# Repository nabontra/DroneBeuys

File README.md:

# DroneBeuys project documentation

#Ceiling String Pull
24vcd stepper motor and fishing line

#Smoke Lamp
12vdc lamp and e-cigarette

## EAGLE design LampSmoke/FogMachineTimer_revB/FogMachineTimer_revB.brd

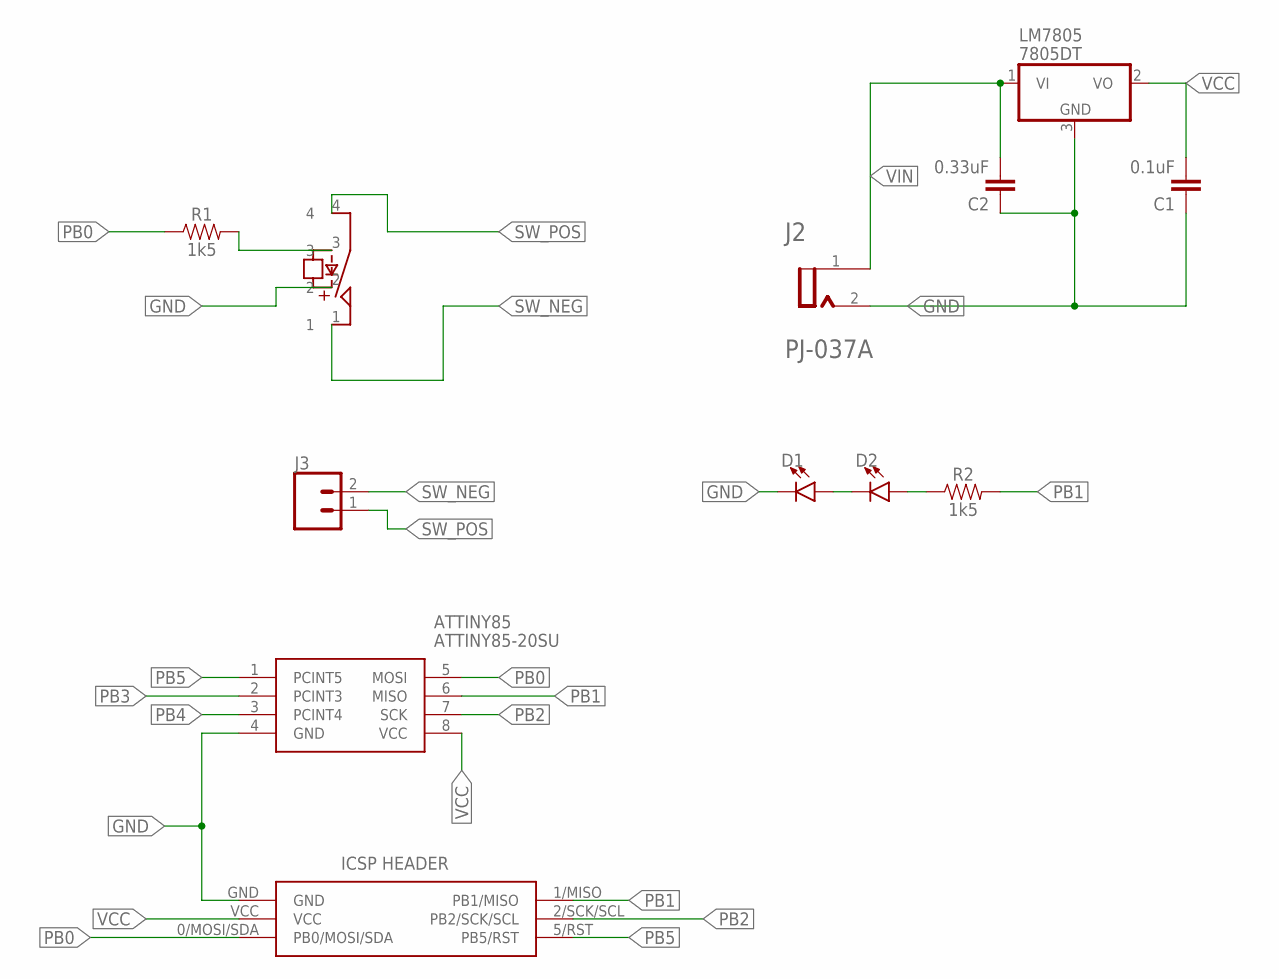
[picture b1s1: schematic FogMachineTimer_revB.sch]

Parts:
ATTINY85: ATTINY85-20SU; SOT127P798X216-8N
C1: 0.1uF; 0603
C2: 0.33uF; 0603
D1, D2: LED1206; LED-1206
J1: M20-9980346; HDRV6W64P254_2X3_762X508X868P
J2: CUI_PJ-037ACUI_PJ-037A_0_0; CUI_PJ-037A_0
J3: CONN_02; 1X02
LM7805: 7805DT; TO252
R1, R2: 1k5; 0603
RELAY: HE3621A0510

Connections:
GND: ATTINY85.4 (GND), C1.1, C2.1, D1.C, J1.GND, J2.2, LM7805.3 (GND), RELAY.2
unnamed: D1.A, D2.C
unnamed: D2.A, R2.1
unnamed: R1.2, RELAY.3
PB0: ATTINY85.5 (MOSI), J1.0/MOSI/SDA (PB0/MOSI/SDA), R1.1
PB1: ATTINY85.6 (MISO), J1.1/MISO (PB1/MISO), R2.2
PB2: ATTINY85.7 (SCK), J1.2/SCK/SCL (PB2/SCK/SCL)
PB3: ATTINY85.2 (PCINT3)
PB4: ATTINY85.3 (PCINT4)
PB5: ATTINY85.1 (PCINT5), J1.5/RST (PB5/RST)
SW_NEG: J3.2, RELAY.1
SW_POS: J3.1, RELAY.4
VCC: ATTINY85.8 (VCC), C1.2, J1.VCC, LM7805.2 (VO)
VIN: C2.2, J2.1, LM7805.1 (VI)

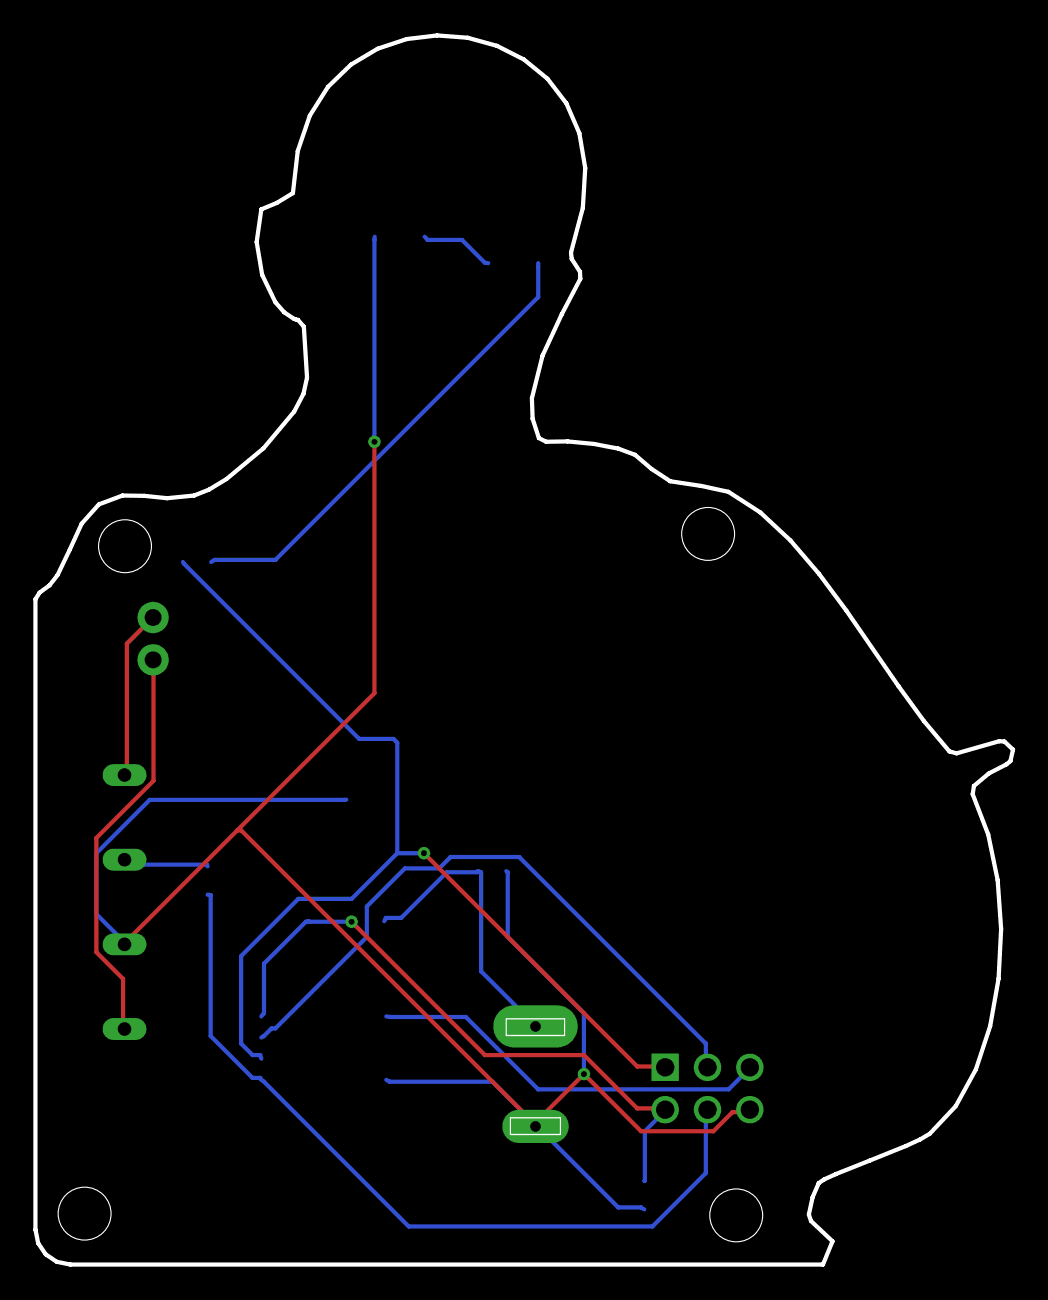
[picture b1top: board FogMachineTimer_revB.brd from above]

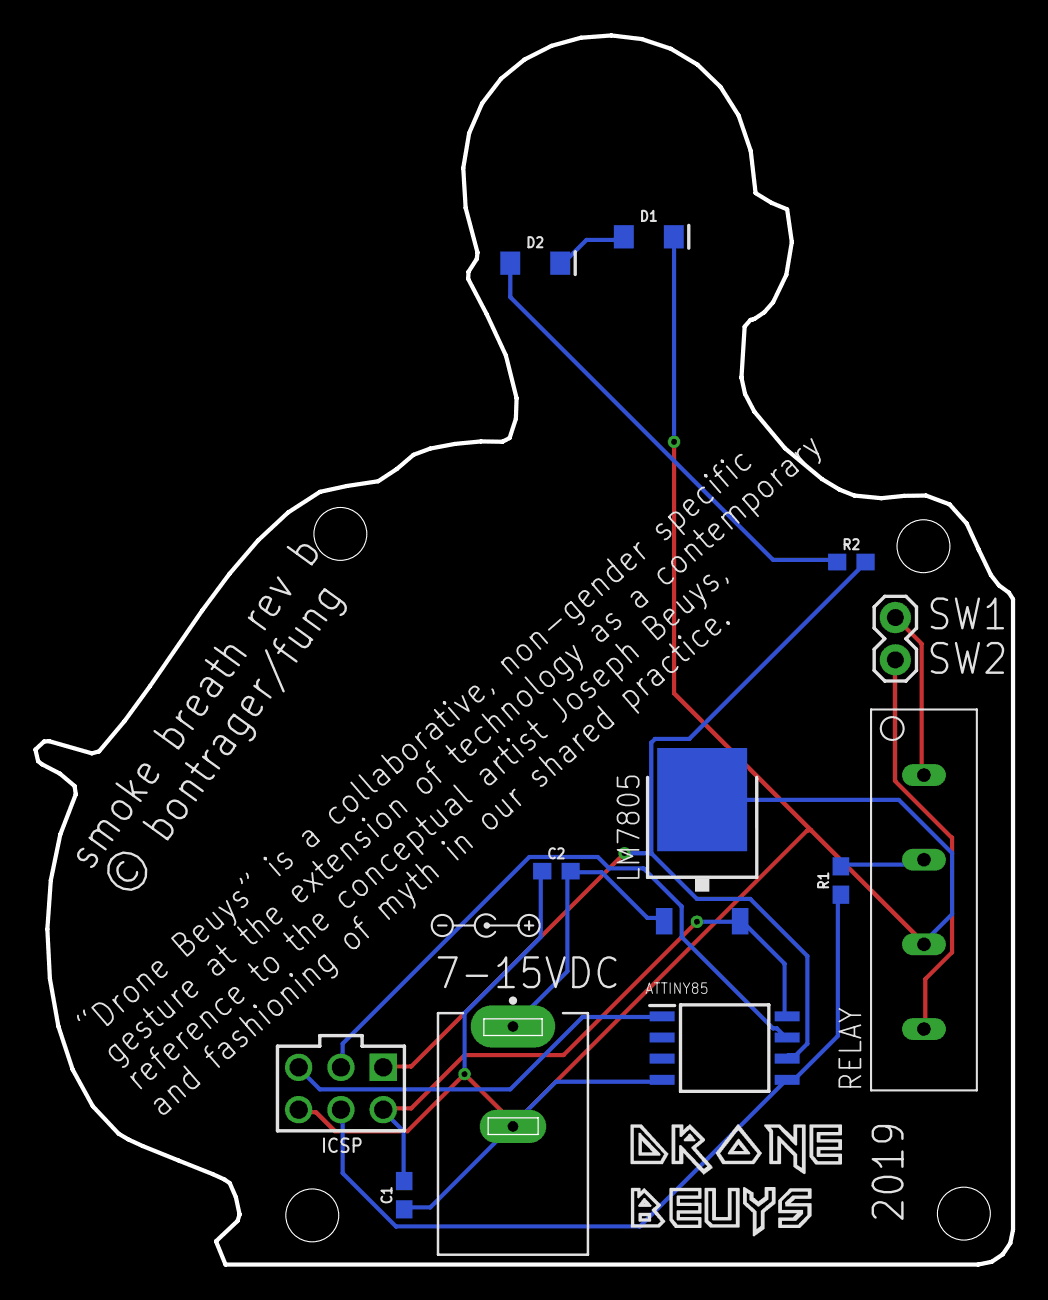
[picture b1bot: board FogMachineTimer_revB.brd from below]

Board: 2 copper layers, 58.7 x 73.8 mm, 14 parts (14 on the bottom side), 12 nets.

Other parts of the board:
U$1: 5VDC_JACK_SILK
U$2: DB_LOGO_MAIDEN

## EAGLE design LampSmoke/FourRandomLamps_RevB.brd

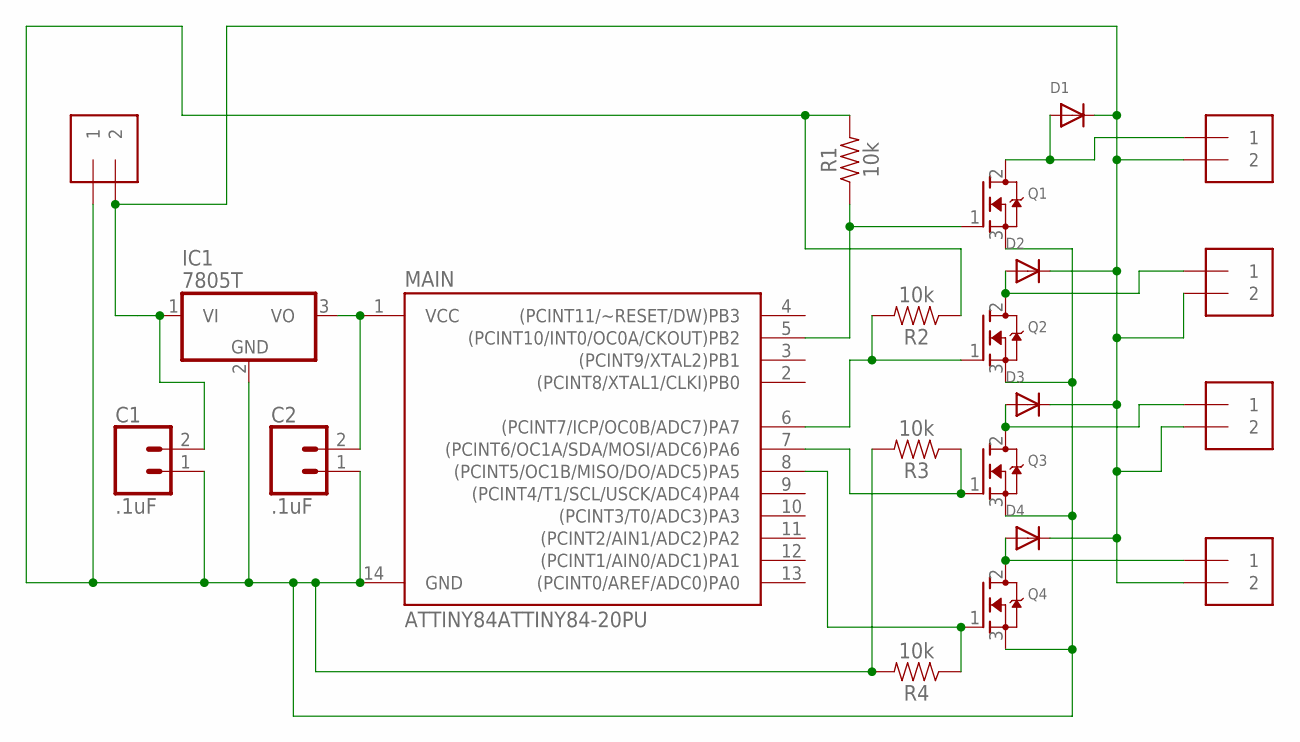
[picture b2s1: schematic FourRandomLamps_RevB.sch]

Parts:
12VDC: 1X2-3.5MM
C1, C2: .1uF; 1X02_LOCK
D1, D2, D3, D4: DIODEDO-1N4148; DO-1N4148
IC1: 7805T; TO220H
LAMP1, LAMP2, LAMP3, LAMP4: 1X2-3.5MM
MAIN: ATTINY84ATTINY84-20PU; DIP14
Q1, Q2, Q3, Q4: MOSFET-NGDS_TO220V; TO220V
R1, R2, R3, R4: 10k; AXIAL-0.3

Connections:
unnamed: C2.2, IC1.3 (VO), MAIN.1 (VCC)
unnamed: 12VDC.2, C1.2, D1.C, D2.C, D3.C, D4.C, IC1.1 (VI), LAMP1.2, LAMP2.2, LAMP3.2, LAMP4.2
unnamed: MAIN.5 ((PCINT10/INT0/OC0A/CKOUT)PB2), Q1.1 (G), R1.P$1 (1)
unnamed: MAIN.6 ((PCINT7/ICP/OC0B/ADC7)PA7), Q2.1 (G), R2.P$2 (2)
unnamed: MAIN.7 ((PCINT6/OC1A/SDA/MOSI/ADC6)PA6), Q3.1 (G), R3.P$1 (1)
unnamed: MAIN.8 ((PCINT5/OC1B/MISO/DO/ADC5)PA5), Q4.1 (G), R4.P$1 (1)
unnamed: 12VDC.1, C1.1, C2.1, IC1.2 (GND), MAIN.14 (GND), Q1.3 (S), Q2.3 (S), Q3.3 (S), Q4.3 (S), R1.P$2 (2), R2.P$1 (1), R3.P$2 (2), R4.P$2 (2)
unnamed: D1.A, LAMP1.1, Q1.2 (D)
unnamed: D2.A, LAMP2.1, Q2.2 (D)
unnamed: D3.A, LAMP3.1, Q3.2 (D)
unnamed: D4.A, LAMP4.1, Q4.2 (D)

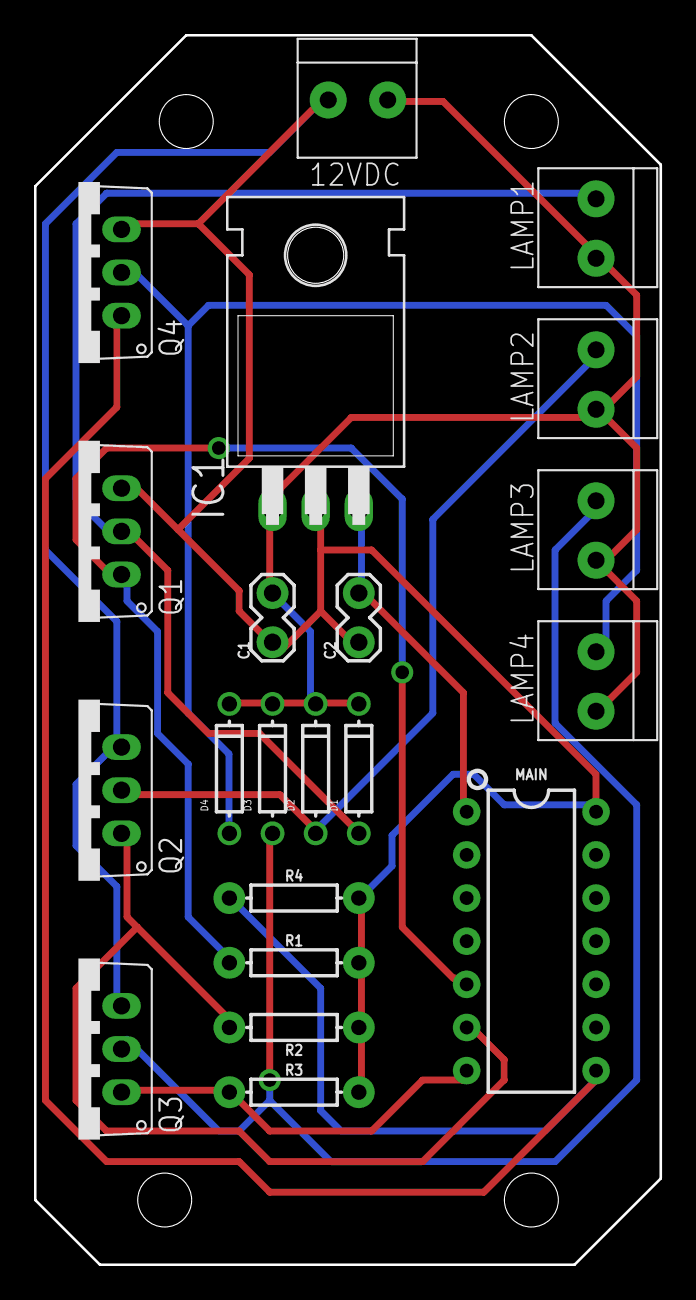
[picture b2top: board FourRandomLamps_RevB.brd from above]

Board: 2 copper layers, 36.8 x 72.4 mm, 21 parts (0 on the bottom side), 11 nets.

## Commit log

2017-10-17 :lollipop: Added .gitattributes & .gitignore files
2017-10-17 Added LampSmoke and CeilingStringPull
2017-10-18 updated pin
2017-10-23 added gerber files
2017-10-28 fogmachine added
2017-11-05 added FourRandomLamps
2018-01-07 showupdate
2019-09-05 adding ssr
2019-09-05 corrected polarity
2019-09-12 FogMachineTimer revB submitted to OSHPark
2019-09-26 added code and power reg
2019-10-03 correct integer limit and changed timing

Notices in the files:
LampSmoke/FogMachineTimer_revB/FogMachineTimer_revB.brd:
© bontrager/fung
parts and their libraries:
SparkFun-Connectors: Licensing: Creative Commons ShareAlike 4.0 International - https://creativecommons.org/licenses/by-sa/4.0
